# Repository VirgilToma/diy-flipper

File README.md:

# DIY Flipper-style Multitool

A handheld, battery-powered hacking and learning multitool inspired by the Flipper Zero, built around an **ESP32-S3**. It brings together Sub-GHz radio, NFC, 125 kHz RFID, infrared, iButton, a microSD card, an OLED display with a D-pad, Wi-Fi and Bluetooth LE on one 130 x 64 mm board, and it will run its own custom firmware.

*Render generated from the KiCad files. The board has not been built yet.*

> **Note:** This is an independent hobby project. It is **not** affiliated with Flipper Devices and is **not** compatible with the official Flipper Zero firmware.

## Project status

| Part | Status | Details |
|---|---|---|
| Hardware (PCB rev 0.5) | Schematic and 2-layer PCB done, ERC and DRC clean. Not ordered or built yet. | [hardware/](hardware/README.md) |
| Firmware | Not started | [firmware/](firmware/README.md) |
| Enclosure | Not started | [enclosure/](enclosure/README.md) |

## What it does

| Function | Hardware |
|---|---|
| MCU, Wi-Fi, Bluetooth LE, USB | ESP32-S3-WROOM-1-N16R2, native USB-C for flashing, serial console and HID |
| Display and controls | 1.3" 128x64 OLED, D-pad (Up / Down / Left / Right / OK) and Back button |
| Sub-GHz radio | CC1101 module |
| NFC (13.56 MHz) | PN532 module |
| RFID (125 kHz) | Discrete reader front end *(experimental)* |
| Infrared | IR receiver and 940 nm IR LED |
| iButton | 1-Wire contacts |
| Storage | microSD card |
| Feedback | RGB LED, buzzer, vibration motor |
| Expansion | 2x9 GPIO header |
| Power | Li-Po battery with USB-C charging |

The full hardware description (schematic, PCB, parts list, assembly and pin map) is in [hardware/README.md](hardware/README.md).

## Repository structure

```
diy-flipper/
├── hardware/     KiCad project of the main PCB (schematic, PCB, symbol library, 3D model)
├── firmware/     custom ESP32-S3 firmware (not started yet)
├── enclosure/    3D-printable case (not started yet)
└── docs/         schematic PDF, bill of materials and the images used in the READMEs
```

Each folder has its own README:

- **[hardware/](hardware/README.md):** how the board works, the PCB, the parts to buy, assembly notes, the ESP32-S3 pin map and the checklist before ordering.
- **[firmware/](firmware/README.md):** target hardware for the firmware, which peripheral sits on which pin, and how to flash the board.
- **[enclosure/](enclosure/README.md):** board dimensions, parts that stick out of the board and the openings the case needs.
- **[docs/](docs/README.md):** what each document and image is and where it comes from.

## Getting started

- **Just looking:** open the [schematic PDF](docs/schematic.pdf) and the [bill of materials](docs/BOM.csv).
- **Editing the board:** install KiCad 10 or newer and open `hardware/diy_flipper.kicad_pro`. Keep the whole `hardware/` folder together.
- **Building one:** read the [hardware README](hardware/README.md), especially [Bill of materials](hardware/README.md#bill-of-materials), [Assembly notes](hardware/README.md#assembly-notes) and [Before ordering the PCB](hardware/README.md#before-ordering-the-pcb).

## Compared with a real Flipper Zero

- Each CC1101 module covers a single Sub-GHz band.
- PN532 card emulation is limited.
- The 125 kHz RFID front end is experimental and will need bench tuning.
- 5 V on the GPIO header is available only while USB is connected.
- No fuel gauge; the battery level is estimated from its voltage.

## Roadmap

- [x] Schematic
- [x] Component placement and 2-layer PCB routing
- [x] Bill of materials and module pinouts checked against the board
- [x] ERC and DRC in KiCad
- [ ] PCB order
- [ ] First prototype build and bring-up
- [ ] Custom firmware (display UI, input, SD card, IR, NFC, Sub-GHz, RFID, iButton)
- [ ] Enclosure

## Responsible use

This device is meant for learning and for working with your own hardware, cards and remotes. Transmitting on radio frequencies, and reading or copying access cards you do not own, may be restricted or illegal where you live. Check your local regulations and only use it on equipment you are authorized to test.

## License

*To be added* (for example CERN-OHL-S for the hardware and enclosure, and MIT or GPL for the firmware).

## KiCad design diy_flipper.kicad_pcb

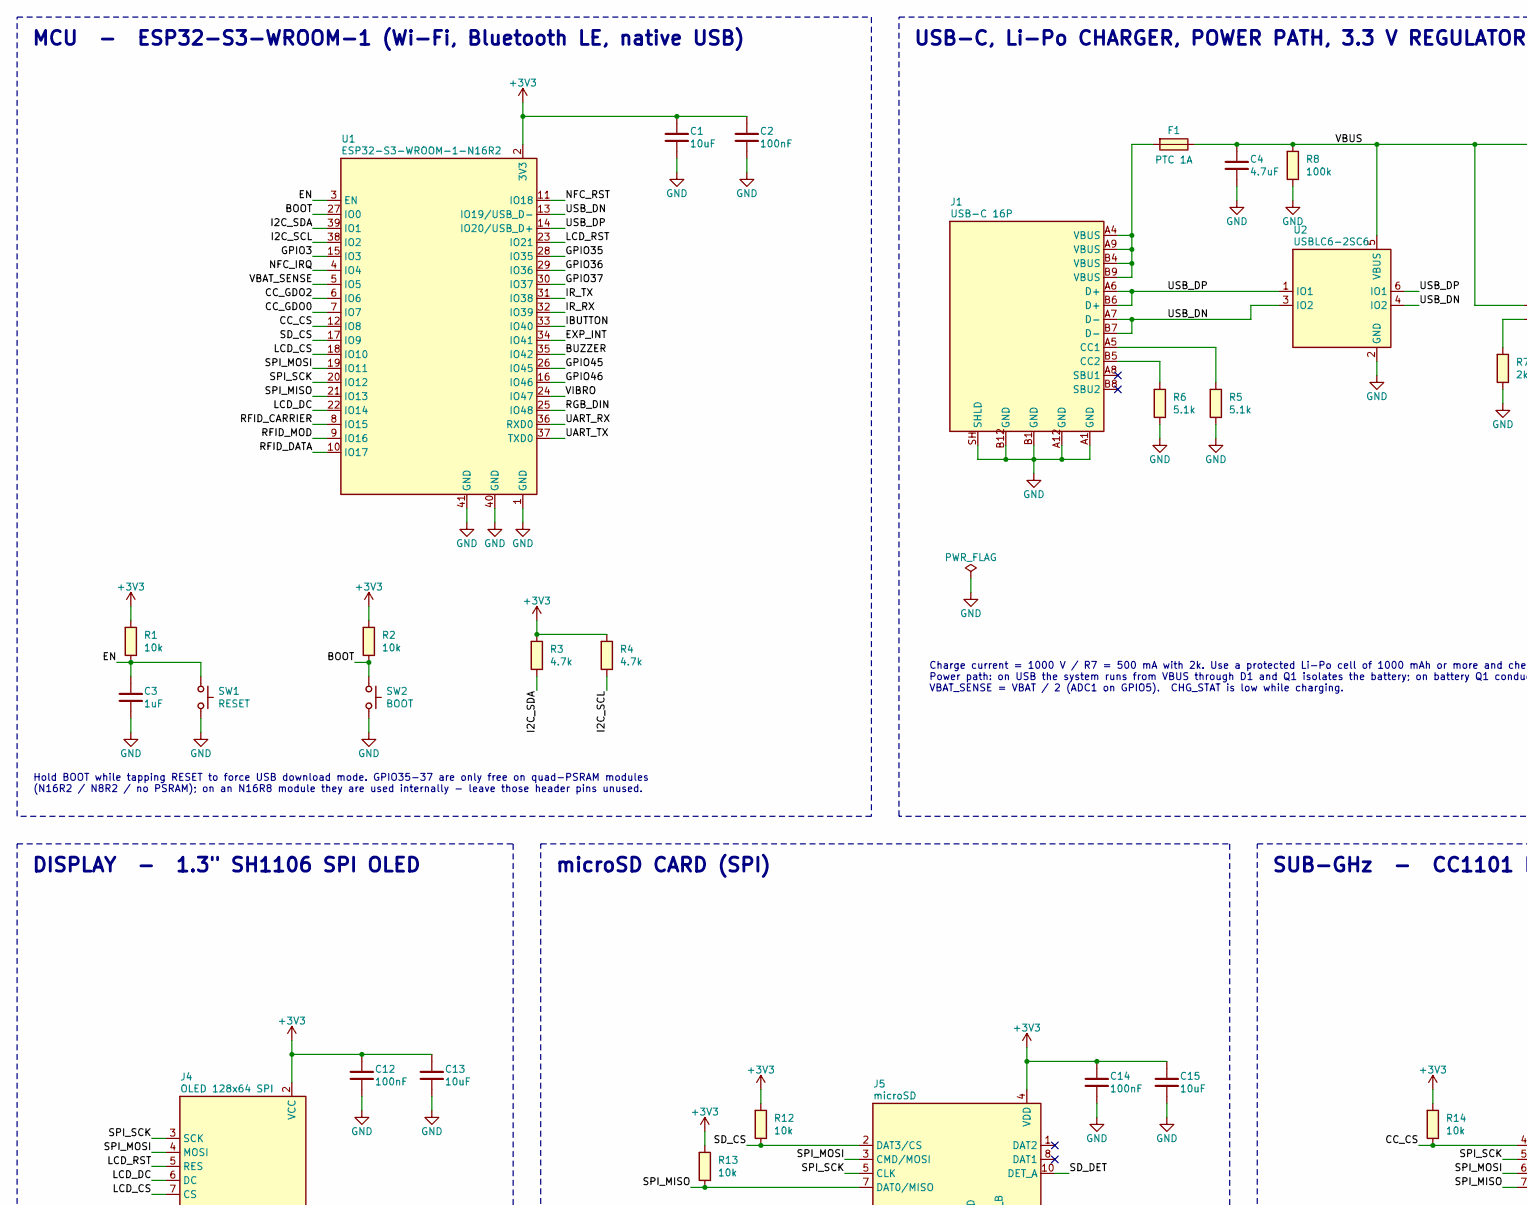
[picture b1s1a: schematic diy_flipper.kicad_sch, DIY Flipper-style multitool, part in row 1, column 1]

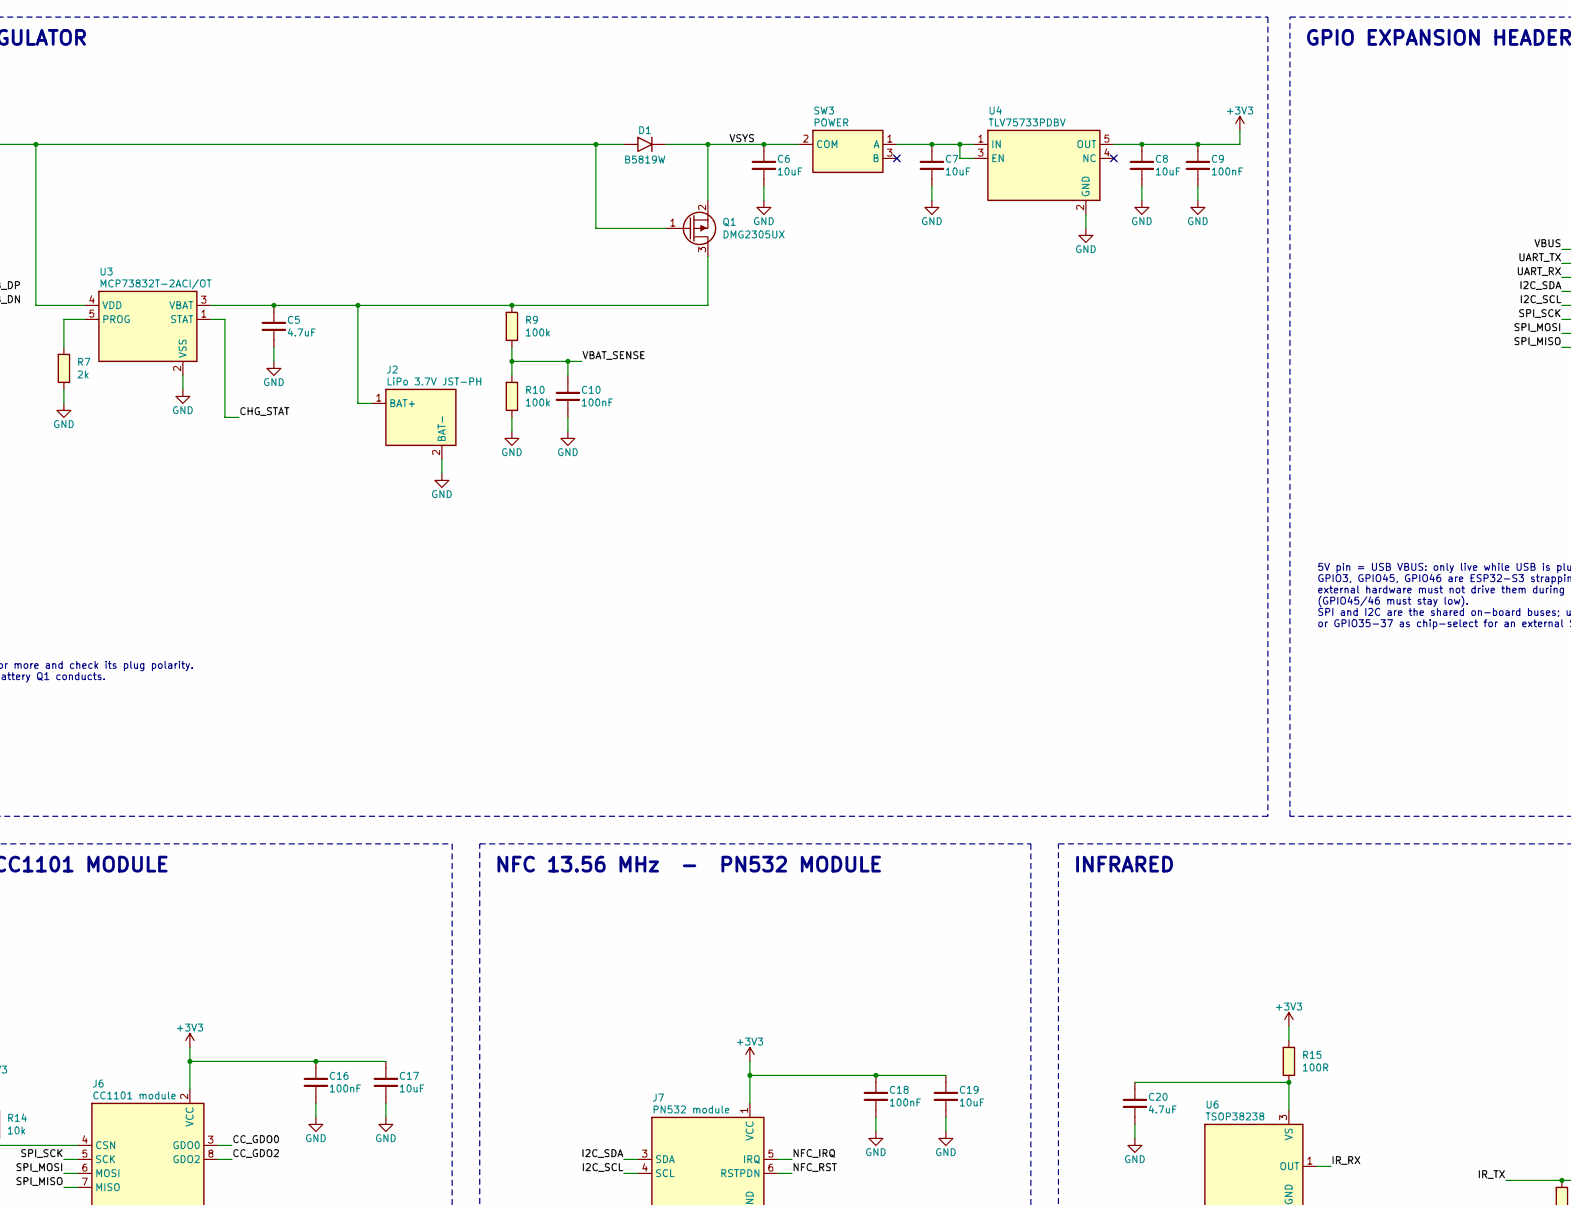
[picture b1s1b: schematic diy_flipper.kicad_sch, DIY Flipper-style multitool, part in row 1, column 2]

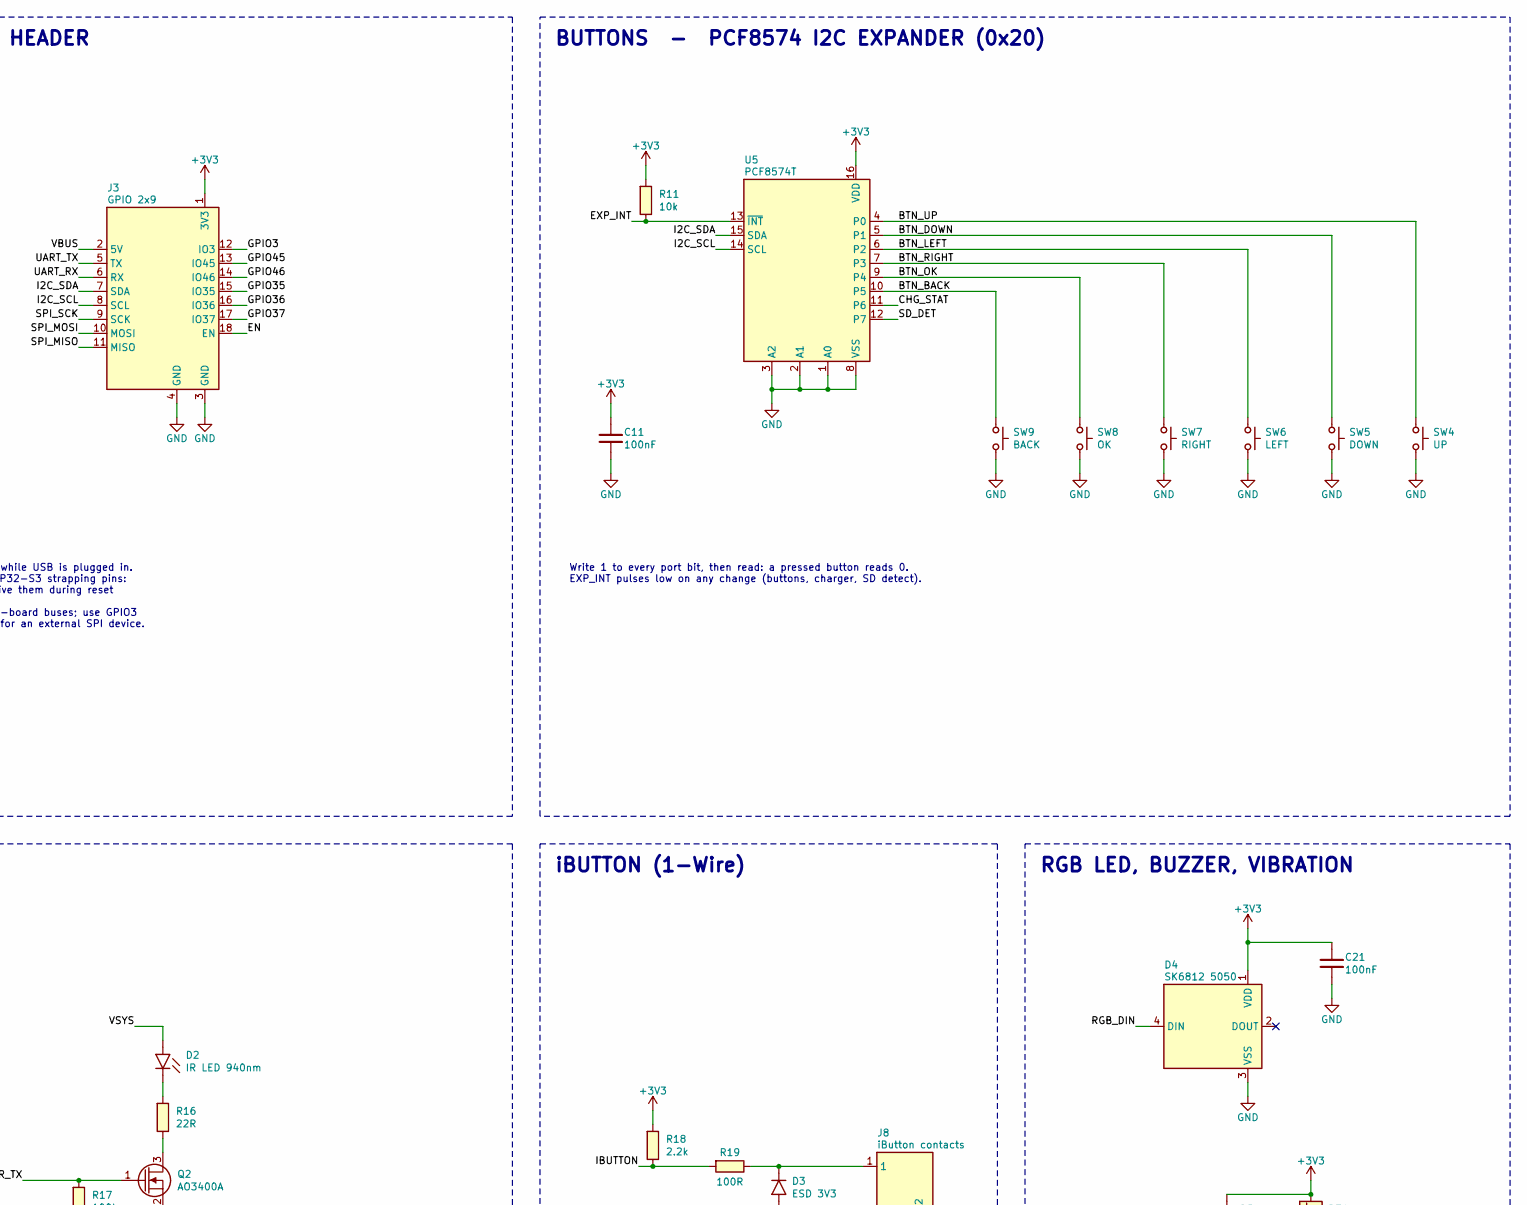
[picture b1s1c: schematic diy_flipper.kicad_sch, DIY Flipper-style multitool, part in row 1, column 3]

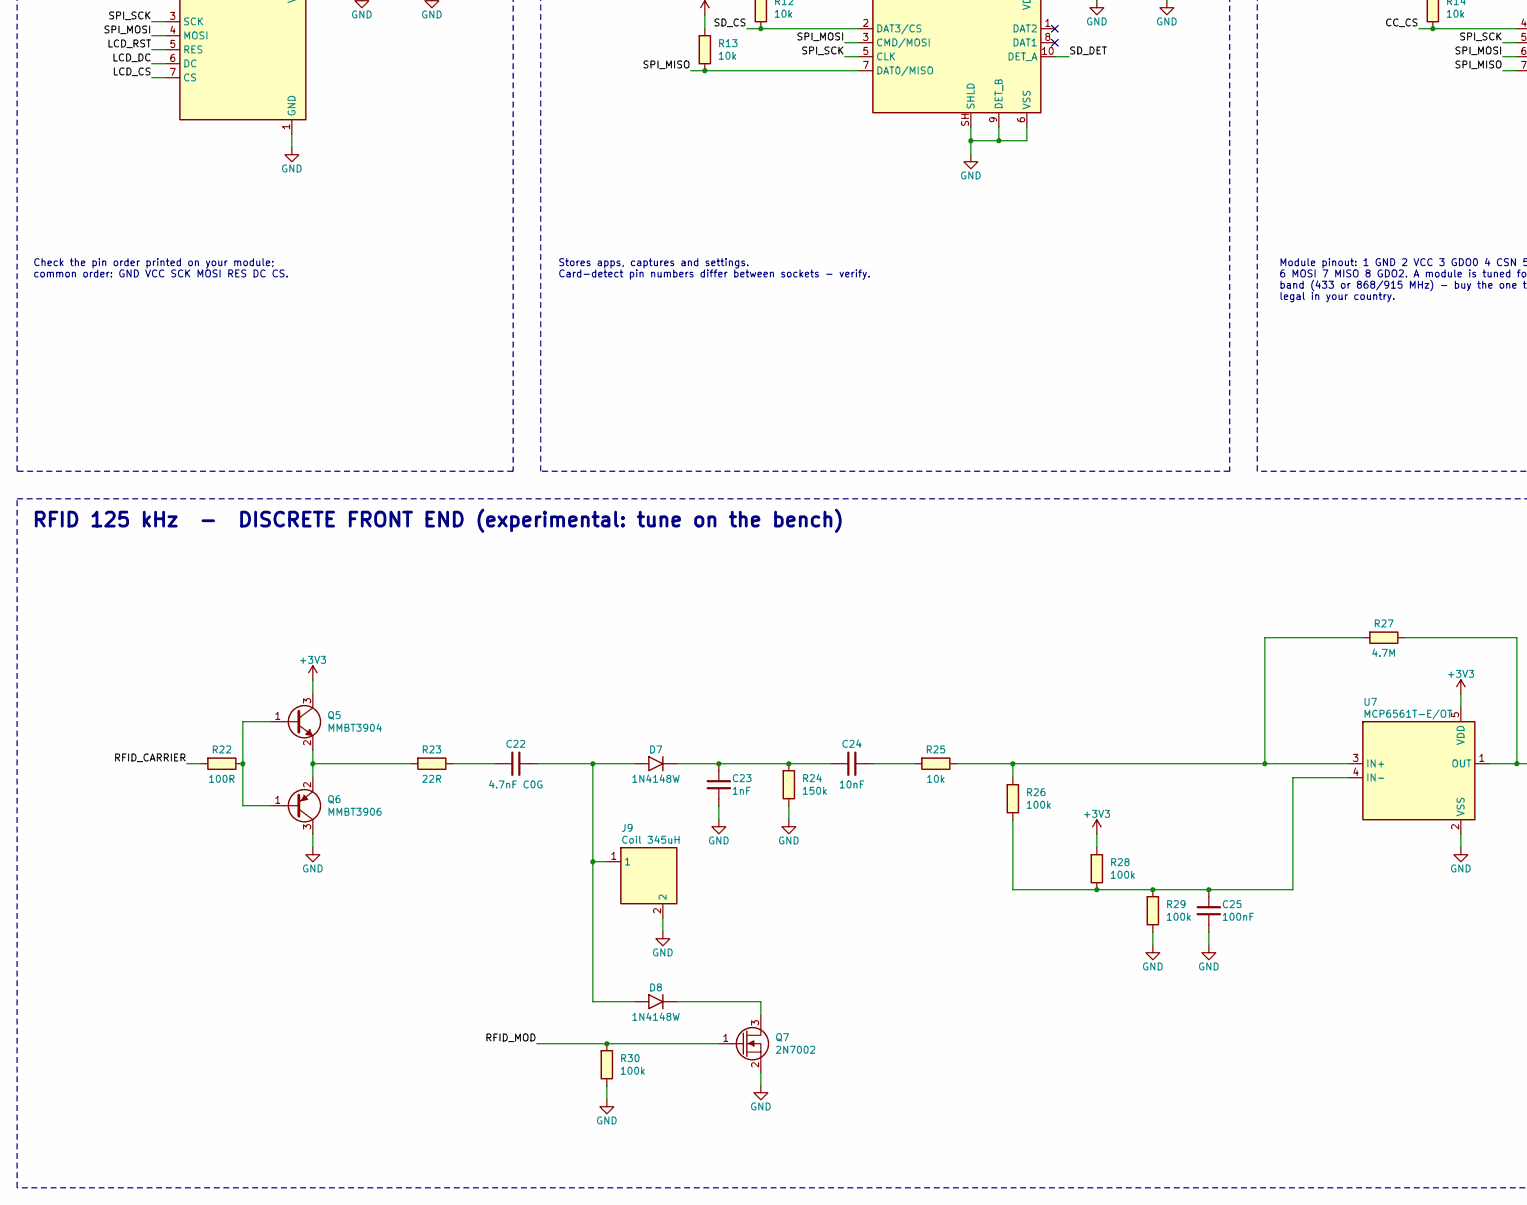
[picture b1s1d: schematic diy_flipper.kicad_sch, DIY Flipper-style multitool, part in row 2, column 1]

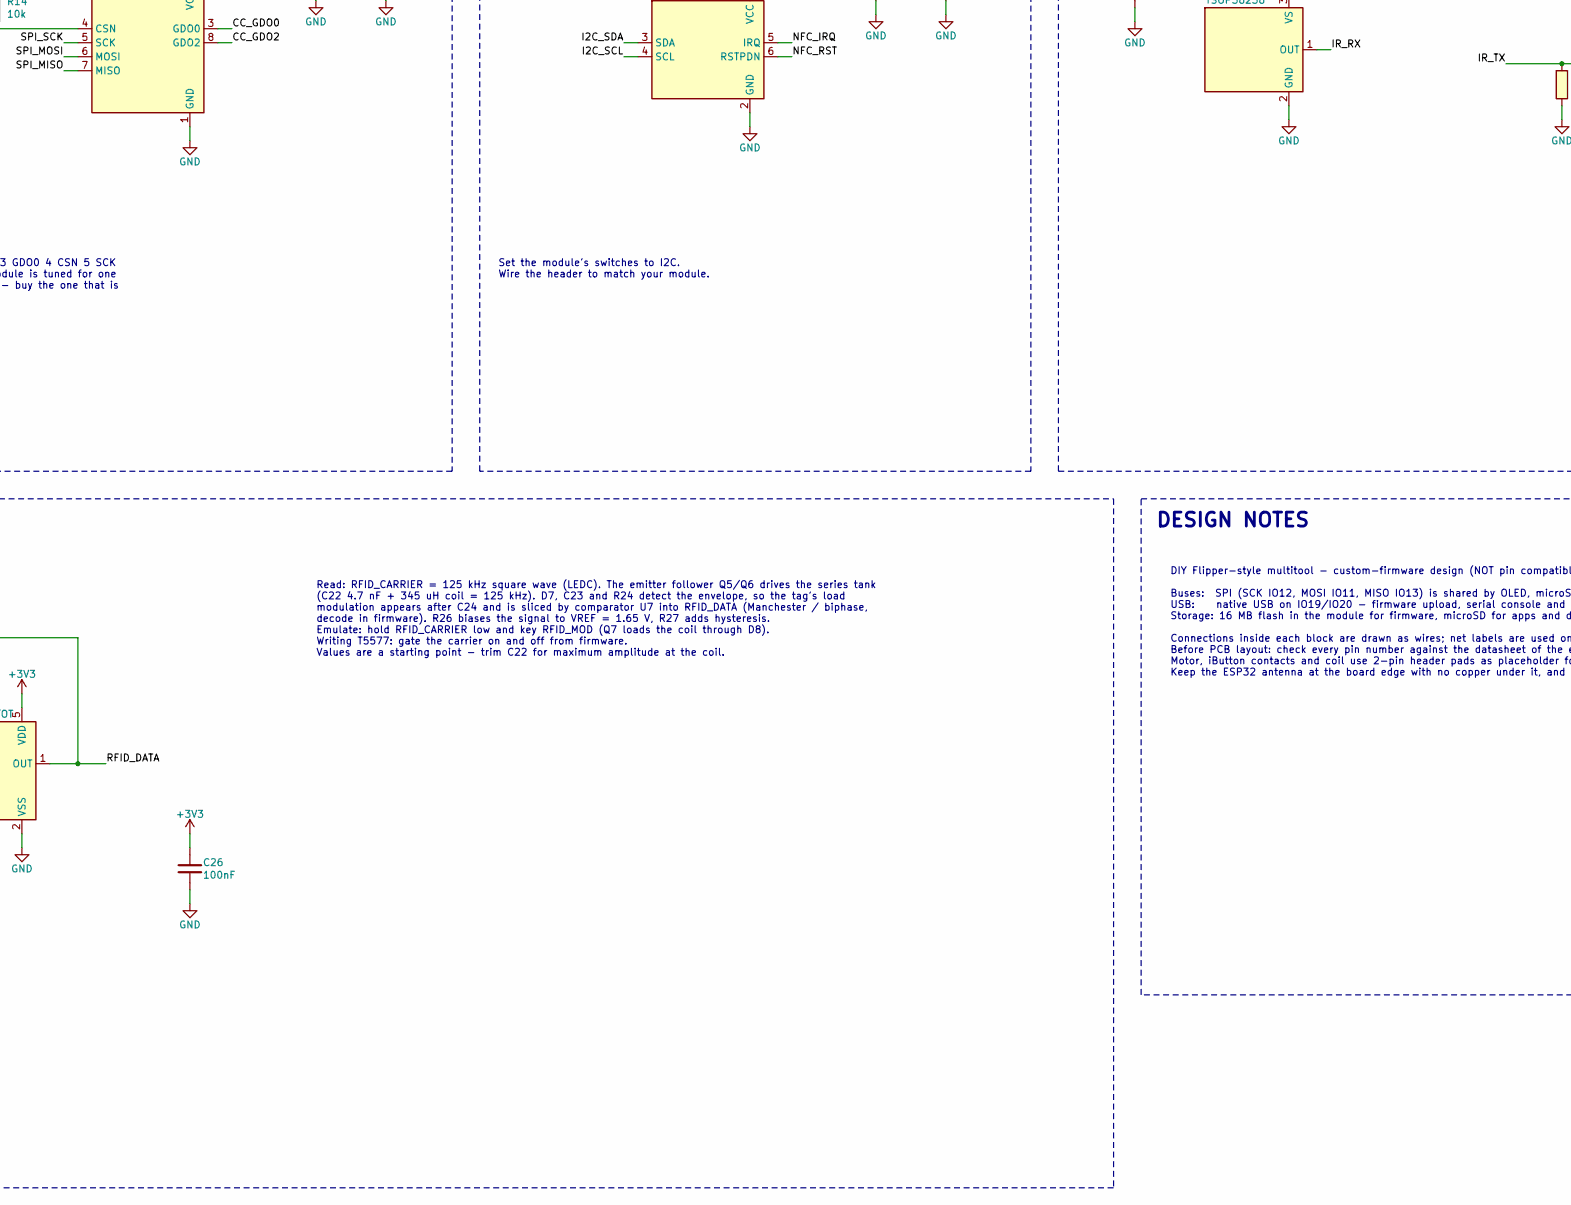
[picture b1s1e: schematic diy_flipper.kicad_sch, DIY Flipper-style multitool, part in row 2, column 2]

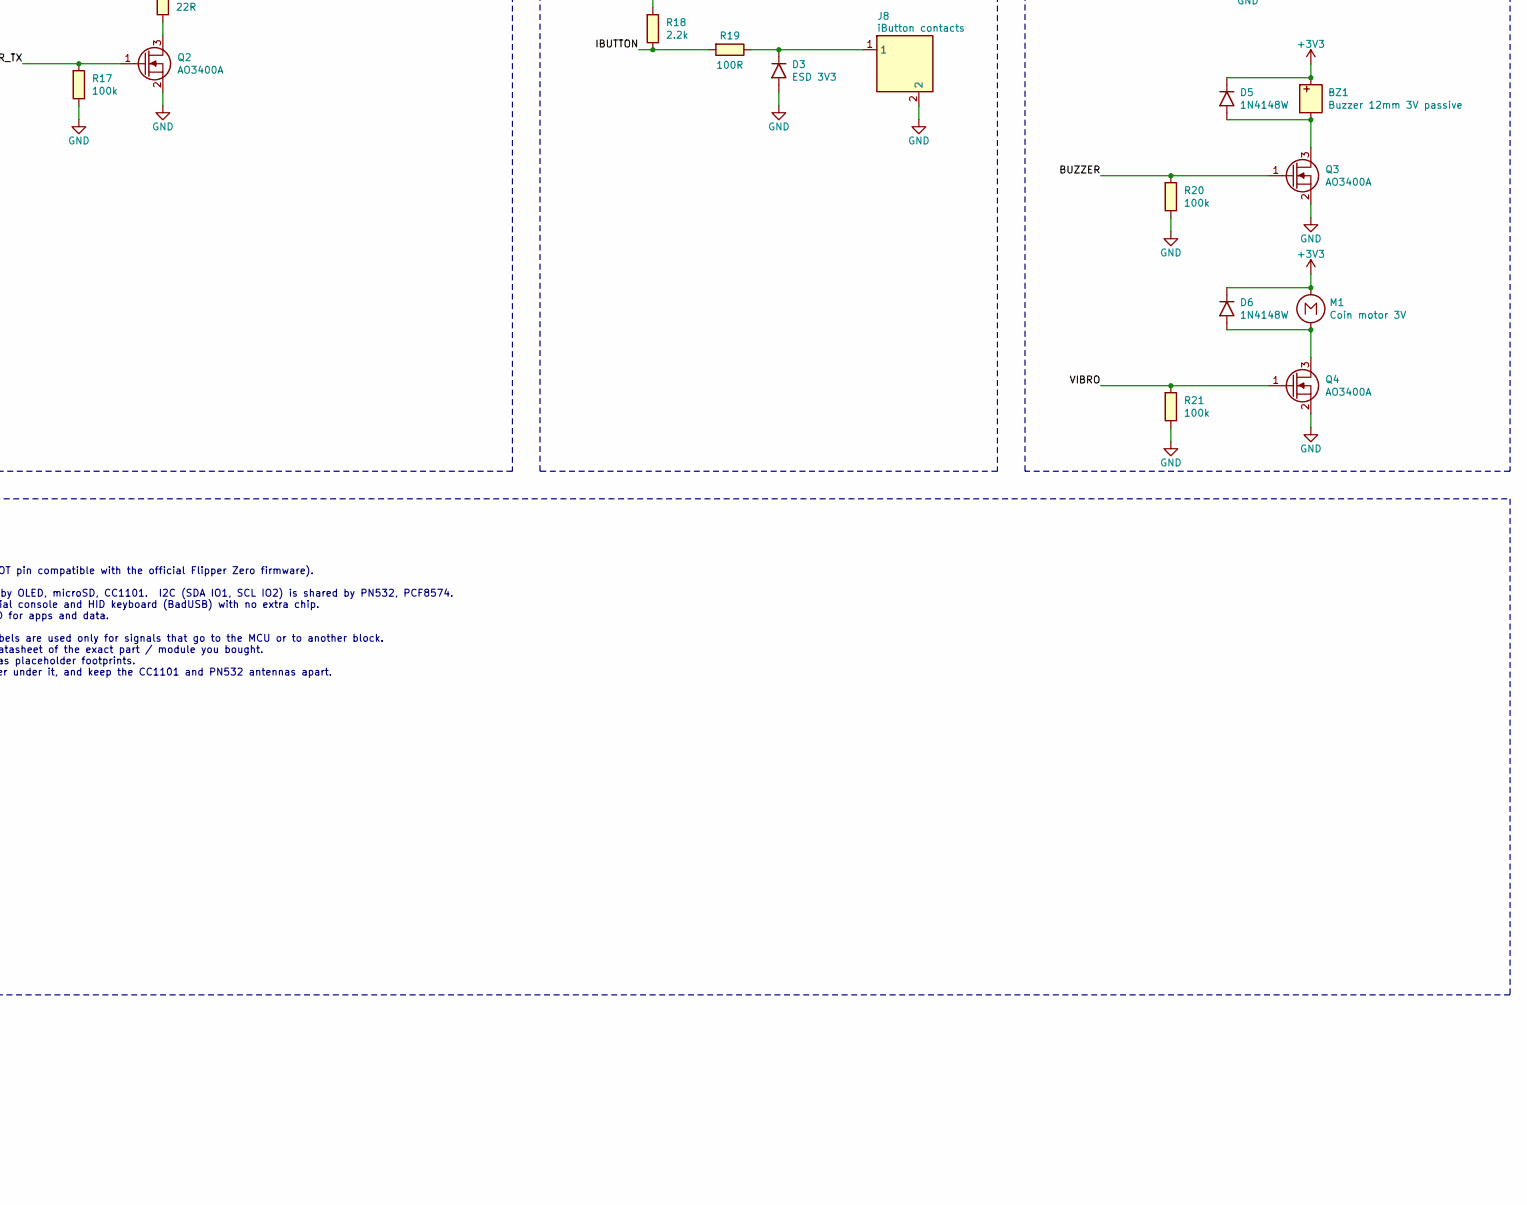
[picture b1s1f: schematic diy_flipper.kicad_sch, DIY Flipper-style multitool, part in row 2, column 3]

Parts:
BZ1: Buzzer 12mm 3V passive; Buzzer_12x9.5RM7.6
C1, C6, C7, C8, C13, C15, C17, C19: 10uF; C_0805_2012Metric
C2, C9, C10, C11, C12, C14, C16, C18, C21, C25, C26: 100nF; C_0603_1608Metric
C3: 1uF; C_0603_1608Metric
C4, C5, C20: 4.7uF; C_0805_2012Metric
C22: 4.7nF C0G; C_0603_1608Metric
C23: 1nF; C_0603_1608Metric
C24: 10nF; C_0603_1608Metric
D1: B5819W; D_SOD-123
D2: IR LED 940nm; LED_D5.0mm
D3: ESD 3V3; D_SOD-323
D4: SK6812 5050; LED_SK6812_PLCC4_5.0x5.0mm_P3.2mm
D5, D6, D7, D8: 1N4148W; D_SOD-123
F1: PTC 1A; Fuse_1206_3216Metric
J1: USB-C 16P; USB_C_Receptacle_HRO_TYPE-C-31-M-12
J2: LiPo 3.7V JST-PH; JST_PH_S2B-PH-K_1x02_P2.00mm_Horizontal
J3: GPIO 2x9; PinHeader_2x09_P2.54mm_Vertical
J4: OLED 128x64 SPI; PinHeader_1x07_P2.54mm_Vertical
J5: microSD; microSD_HC_Hirose_DM3AT-SF-PEJM5
J6: CC1101 module; PinHeader_2x04_P2.54mm_Vertical
J7: PN532 module; PinHeader_1x06_P2.54mm_Vertical
J8: iButton contacts; PinHeader_1x02_P2.54mm_Vertical
J9: Coil 345uH; PinHeader_1x02_P2.54mm_Vertical
M1: Coin motor 3V; PinHeader_1x02_P2.54mm_Vertical
Q1: DMG2305UX; SOT-23
Q2, Q3, Q4: AO3400A; SOT-23
Q5: MMBT3904; SOT-23
Q6: MMBT3906; SOT-23
Q7: 2N7002; SOT-23
R1, R2, R11, R12, R13, R14, R25: 10k; R_0603_1608Metric
R3, R4: 4.7k; R_0603_1608Metric
R5, R6: 5.1k; R_0603_1608Metric
R7: 2k; R_0603_1608Metric
R8, R9, R10, R17, R20, R21, R26, R28, R29, R30: 100k; R_0603_1608Metric
R15, R19, R22: 100R; R_0603_1608Metric
R16: 22R; R_1206_3216Metric
R18: 2.2k; R_0603_1608Metric
R23: 22R; R_0603_1608Metric
R24: 150k; R_0603_1608Metric
R27: 4.7M; R_0603_1608Metric
SW1: RESET; SW_PUSH_6mm
SW2: BOOT; SW_PUSH_6mm
SW3: POWER; SW_SPDT_PCM12
SW4: UP; SW_PUSH_6mm
SW5: DOWN; SW_PUSH_6mm
SW6: LEFT; SW_PUSH_6mm
SW7: RIGHT; SW_PUSH_6mm
SW8: OK; SW_PUSH_6mm
SW9: BACK; SW_PUSH_6mm
U1: ESP32-S3-WROOM-1-N16R2; ESP32-S3-WROOM-1
U2: USBLC6-2SC6; SOT-23-6
U3: MCP73832T-2ACI/OT; SOT-23-5
U4: TLV75733PDBV; SOT-23-5
U5: PCF8574T; SOIC-16W_7.5x10.3mm_P1.27mm
U6: TSOP38238; Vishay_MINICAST-3Pin
U7: MCP6561T-E/OT; SOT-23-5

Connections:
+3V3: BZ1.1, C1.1, C2.1, C8.1, C9.1, C11.1, C12.1, C13.1, C14.1, C15.1, C16.1, C17.1, C18.1, C19.1, C21.1, C26.1, D4.1 (VDD), D5.1, D6.1, J3.1 (3V3), J4.2 (VCC), J5.4 (VDD), J6.2 (VCC), J7.1 (VCC), M1.1, Q5.3, R1.1, R2.1, R3.1, R4.1, R11.1, R12.1, R13.1, R14.1, R15.1, R18.1, R28.1, U1.2 (3V3), U4.5 (OUT), U5.16 (VDD), U7.5 (VDD)
/BOOT: R2.2, SW2.1, U1.27 (IO0)
/BTN_BACK: SW9.1, U5.10 (P5)
/BTN_DOWN: SW5.1, U5.5 (P1)
/BTN_LEFT: SW6.1, U5.6 (P2)
/BTN_OK: SW8.1, U5.9 (P4)
/BTN_RIGHT: SW7.1, U5.7 (P3)
/BTN_UP: SW4.1, U5.4 (P0)
/BUZZER: Q3.1, R20.1, U1.35 (IO42)
/BUZ_D: BZ1.2, D5.2, Q3.3
/CC_CS: J6.4 (CSN), R14.2, U1.12 (IO8)
/CC_GDO0: J6.3 (GDO0), U1.7 (IO7)
/CC_GDO2: J6.8 (GDO2), U1.6 (IO6)
/CHG_PROG: R7.1, U3.5 (PROG)
/CHG_STAT: U3.1 (STAT), U5.11 (P6)
/EN: C3.1, J3.18 (EN), R1.2, SW1.1, U1.3 (EN)
/EXP_INT: R11.2, U1.34 (IO41), U5.13 (~INT)
/GPIO3: J3.12 (IO3), U1.15 (IO3)
/GPIO35: J3.15 (IO35), U1.28 (IO35)
/GPIO36: J3.16 (IO36), U1.29 (IO36)
/GPIO37: J3.17 (IO37), U1.30 (IO37)
/GPIO45: J3.13 (IO45), U1.26 (IO45)
/GPIO46: J3.14 (IO46), U1.16 (IO46)
/I2C_SCL: J3.8 (SCL), J7.4 (SCL), R4.2, U1.38 (IO2), U5.14 (SCL)
/I2C_SDA: J3.7 (SDA), J7.3 (SDA), R3.2, U1.39 (IO1), U5.15 (SDA)
/IBTN_PAD: D3.1, J8.1, R19.2
/IBUTTON: R18.2, R19.1, U1.33 (IO40)
/IR_DRAIN: Q2.3, R16.2
/IR_LED_K: D2.1, R16.1
/IR_RX: U1.32 (IO39), U6.1 (OUT)
/IR_TX: Q2.1, R17.1, U1.31 (IO38)
/IR_VS: C20.1, R15.2, U6.3 (VS)
/LCD_CS: J4.7 (CS), U1.18 (IO10)
/LCD_DC: J4.6 (DC), U1.22 (IO14)
/LCD_RST: J4.5 (RES), U1.23 (IO21)
/NFC_IRQ: J7.5 (IRQ), U1.4 (IO4)
/NFC_RST: J7.6 (RSTPDN), U1.11 (IO18)
/RFID_AC: C24.2, R25.1
/RFID_ANT: C22.2, D7.2, D8.2, J9.1
/RFID_BASE: Q5.1, Q6.1, R22.2
/RFID_CARRIER: R22.1, U1.8 (IO15)
/RFID_DRV: Q5.2, Q6.2, R23.1
/RFID_EMU_D: D8.1, Q7.3
/RFID_ENV: C23.1, C24.1, D7.1, R24.1
/RFID_MOD: Q7.1, R30.1, U1.9 (IO16)
/RFID_TANK: C22.1, R23.2
/RFID_VREF: C25.1, R26.2, R28.2, R29.1, U7.4 (IN-)
/RGB_DIN: D4.4 (DIN), U1.25 (IO48)
/SD_CS: J5.2 (DAT3/CS), R12.2, U1.17 (IO9)
/SD_DET: J5.10 (DET_A), U5.12 (P7)
/SPI_MISO: J3.11 (MISO), J5.7 (DAT0/MISO), J6.7 (MISO), R13.2, U1.21 (IO13)
/SPI_MOSI: J3.10 (MOSI), J4.4 (MOSI), J5.3 (CMD/MOSI), J6.6 (MOSI), U1.19 (IO11)
/SPI_SCK: J3.9 (SCK), J4.3 (SCK), J5.5 (CLK), J6.5 (SCK), U1.20 (IO12)
/UART_RX: J3.6 (RX), U1.36 (RXD0)
/UART_TX: J3.5 (TX), U1.37 (TXD0)
/USB_CC1: J1.A5 (CC1), R5.1
/USB_CC2: J1.B5 (CC2), R6.1
/USB_DN: J1.A7 (D-), J1.B7 (D-), U1.13 (IO19/USB_D-), U2.3 (IO2), U2.4 (IO2)
/USB_DP: J1.A6 (D+), J1.B6 (D+), U1.14 (IO20/USB_D+), U2.1 (IO1), U2.6 (IO1)
/USB_VBUS: F1.1, J1.A4 (VBUS), J1.A9 (VBUS), J1.B4 (VBUS), J1.B9 (VBUS)
/VBAT: C5.1, J2.1 (BAT+), Q1.3, R9.1, U3.3 (VBAT)
/VBAT_SENSE: C10.1, R9.2, R10.1, U1.5 (IO5)
/VBUS: C4.1, D1.2, F1.2, J3.2 (5V), Q1.1, R8.1, U2.5 (VBUS), U3.4 (VDD)
/VIBRO: Q4.1, R21.1, U1.24 (IO47)
/VIB_D: D6.2, M1.2, Q4.3
/VSW: C7.1, SW3.1 (A), U4.1 (IN), U4.3 (EN)
/VSYS: C6.1, D1.1, D2.2, Q1.2, SW3.2 (COM)
GND: C1.2, C2.2, C3.2, C4.2, C5.2, C6.2, C7.2, C8.2, C9.2, C10.2, C11.2, C12.2, C13.2, C14.2, C15.2, C16.2, C17.2, C18.2, C19.2, C20.2, C21.2, C23.2, C25.2, C26.2, D3.2, D4.3 (VSS), J1.A1 (GND), J1.A12 (GND), J1.B1 (GND), J1.B12 (GND), J1.SH (SHLD), J2.2 (BAT-), J3.3 (GND), J3.4 (GND), J4.1 (GND), J5.6 (VSS), J5.9 (DET_B), J5.SH (SHLD), J6.1 (GND), J7.2 (GND), J8.2, J9.2, Q2.2, Q3.2, Q4.2, Q6.3, Q7.2, R5.2, R6.2, R7.2, R8.2, R10.2, R17.2, R20.2, R21.2, R24.2, R29.2, R30.2, SW1.2, SW2.2, SW4.2, SW5.2, SW6.2, SW7.2, SW8.2, SW9.2, U1.1 (GND), U1.40 (GND), U1.41 (GND), U2.2 (GND), U3.2 (VSS), U4.2 (GND), U5.1 (A0), U5.2 (A1), U5.3 (A2), U5.8 (VSS), U6.2 (GND), U7.2 (VSS)

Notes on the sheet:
Set the module's switches to I2C. Wire the header to match your module.
Stores apps, captures and settings. Card-detect pin numbers differ between sockets - verify.
SUB-GHz - CC1101 MODULE
DIY Flipper-style multitool - custom-firmware design (NOT pin compatible with the official Flipper Zero firmware). Buses: SPI (SCK IO12, MOSI IO11, MISO IO13) is shared by OLED, microSD, CC1101. I2C (SDA IO1, SCL IO2) is shared by PN532, PCF8574. USB: native USB on IO19/IO20 - firmware upload, seri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
GPIO EXPANSION HEADER
Write 1 to every port bit, then read: a pressed button reads 0. EXP_INT pulses low on any change (buttons, charger, SD detect).
DESIGN NOTES
Check the pin order printed on your module; common order: GND VCC SCK MOSI RES DC CS.
microSD CARD (SPI)
RFID 125 kHz - DISCRETE FRONT END (experimental: tune on the bench)
DISPLAY - 1.3" SH1106 SPI OLED
Hold BOOT while tapping RESET to force USB download mode. GPIO35-37 are only free on quad-PSRAM modules (N16R2 / N8R2 / no PSRAM); on an N16R8 module they are used internally - leave those header pins unused.
Read: RFID_CARRIER = 125 kHz square wave (LEDC). The emitter follower Q5/Q6 drives the series tank (C22 4.7 nF + 345 uH coil = 125 kHz). D7, C23 and R24 detect the envelope, so the tag's load modulation appears after C24 and is sliced by comparator U7 into RFID_DATA (Manchester / biphase, decode in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
NFC 13.56 MHz - PN532 MODULE
iBUTTON (1-Wire)
Charge current = 1000 V / R7 = 500 mA with 2k. Use a protected Li-Po cell of 1000 mAh or more and check its plug polarity. Power path: on USB the system runs from VBUS through D1 and Q1 isolates the battery; on battery Q1 conducts. VBAT_SENSE = VBAT / 2 (ADC1 on GPIO5). CHG_STAT is low while chargi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
MCU - ESP32-S3-WROOM-1 (Wi-Fi, Bluetooth LE, native USB)
INFRARED
USB-C, Li-Po CHARGER, POWER PATH, 3.3 V REGULATOR
BUTTONS - PCF8574 I2C EXPANDER (0x20)
5V pin = USB VBUS: only live while USB is plugged in. GPIO3, GPIO45, GPIO46 are ESP32-S3 strapping pins: external hardware must not drive them during reset (GPIO45/46 must stay low). SPI and I2C are the shared on-board buses; use GPIO3 or GPIO35-37 as chip-select for an external SPI device.
Module pinout: 1 GND 2 VCC 3 GDO0 4 CSN 5 SCK 6 MOSI 7 MISO 8 GDO2. A module is tuned for one band (433 or 868/915 MHz) - buy the one that is legal in your country.
RGB LED, BUZZER, VIBRATION

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
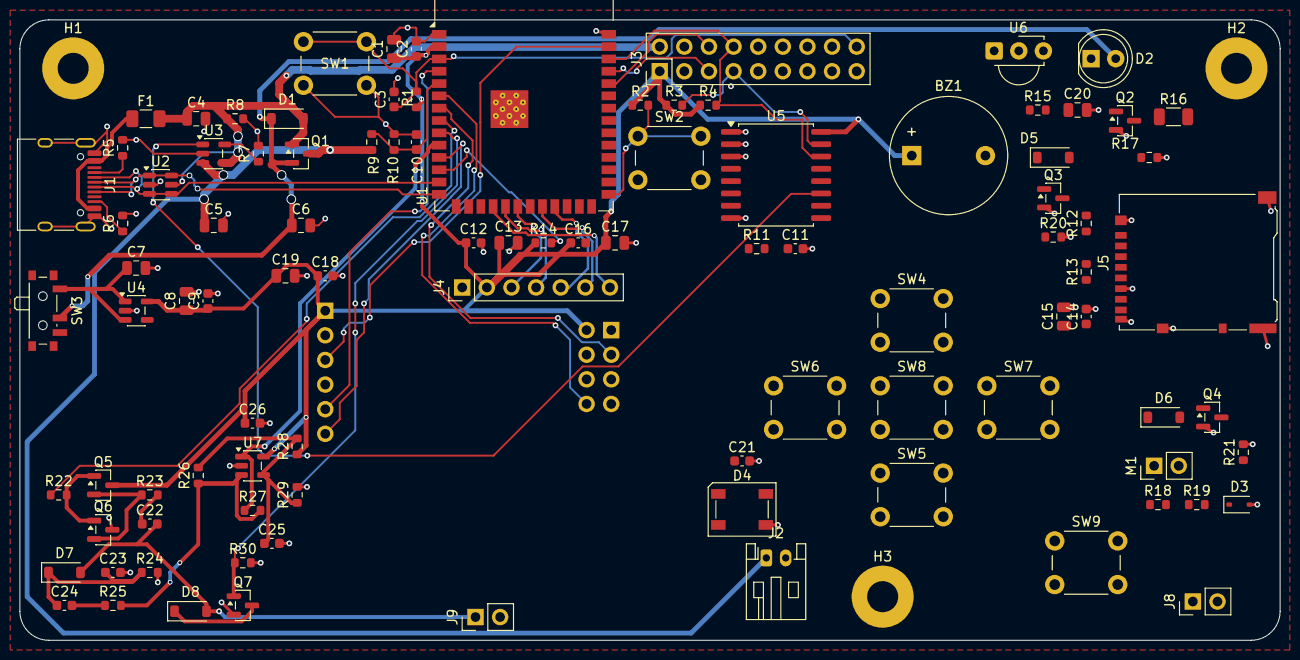
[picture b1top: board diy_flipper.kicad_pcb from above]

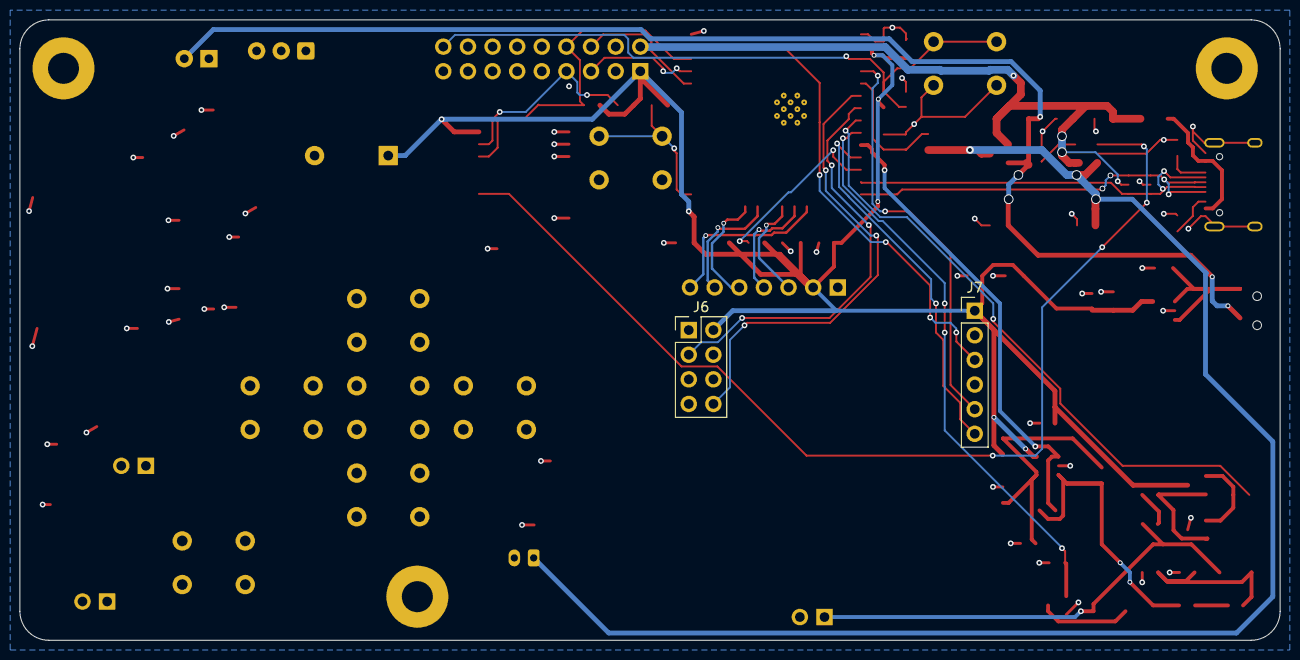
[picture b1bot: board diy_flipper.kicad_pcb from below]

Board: 2 copper layers, 130.0 x 64.0 mm, 102 parts (2 on the bottom side), 70 nets.

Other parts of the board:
H1, H2, H3: MountingHole_3.2mm_M3_Pad

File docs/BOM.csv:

Reference,Qty,Part,Package,Suggested part number,Function,Notes
U1,1,ESP32-S3-WROOM-1-N16R2,SMD module 18 x 25.5 mm,Espressif ESP32-S3-WROOM-1-N16R2,"MCU, Wi-Fi, BLE, USB","Exactly N16R2 (16 MB flash, 2 MB quad PSRAM). Not N16R8 / N8R8: on those GPIO35-37 are used by the octal PSRAM."
J4 (module),1,"1.3"" OLED 128x64, SH1106, SPI, 7 pins",module 35.4 x 33.5 mm,"Pololu 3761 or equivalent ""1.3 inch OLED SPI 7 pin SH1106""",Display,"Pin order must be GND, VCC, CLK, MOSI, RES, DC, CS. Not the 4-pin I2C version. Soldered straight into J4 (no socket)."
J6 (module),1,"CC1101 433 MHz module, 2x4 header",module 15 x 30 mm (+ SMA),EBYTE E07-M1101D-SMA (or E07-M1101D-TH with spring antenna),Sub-GHz radio,"3.6 V max. Generic CC1101 boards use other pin orders: buy the E07. Mounted on the back, see the assembly notes."
J7 (module),1,PN532 NFC module V3 (or V4),module 42.7 x 40.4 mm,Elechouse PN532 NFC Module V3/V4 or the red V3 clone,NFC 13.56 MHz,"I2C mode: S1 = ON, S2 = OFF. Wired to J7 (1x5: GND, VCC, SDA, SCL, IRQ); pins 1-4 follow the module I2C header, IRQ comes from the module top header."
J7 (board),1,"Pin header 1x5, 2.54 mm",THT,-,PN532 connection,Optional: the wires can also be soldered straight into the holes.
BT1 (off board),1,Li-Po 3.7 V 503450 (~1000 mAh) with protection,"50 x 34 x 5 mm, JST-PH 2.0 plug",any 503450 with PCM and JST-PH plug,Power,"Polarity: pin 1 = + (red wire), as on SparkFun/Adafruit. Many RC batteries are reversed: check with a multimeter first."
U2,1,USBLC6-2SC6,SOT-23-6,STMicroelectronics USBLC6-2SC6,USB ESD protection,
U3,1,MCP73832T-2ACI/OT,SOT-23-5,Microchip MCP73832T-2ACI/OT,"Li-Po charger, ~500 mA (R7 = 2 kOhm)",-2A variant = 4.20 V. STAT output is open-drain.
U4,1,TLV75733PDBVR,SOT-23-5 (DBV),Texas Instruments TLV75733PDBVR,"3.3 V LDO, 1 A",DBV package (not DYD/DRV).
U5,1,PCF8574T,SO-16 wide (7.5 mm),NXP PCF8574T/3 or TI PCF8574DWR,"Button expander, I2C 0x20",Not PCF8574A: its address is 0x38.
U6,1,TSOP38238,"Minicast, THT",Vishay TSOP38238,38 kHz IR receiver,TSOP382xx / 384xx family only: other TSOP families swap VS and GND.
U7,1,MCP6561T-E/OT,SOT-23-5,Microchip MCP6561T-E/OT,125 kHz RFID comparator,Not MCP6561R or MCP6561U: different pinout.
Q1,1,DMG2305UX,SOT-23,Diodes Inc. DMG2305UX-7,"P-MOSFET, USB / battery switch-over",
"Q2, Q3, Q4",3,AO3400A,SOT-23,Alpha & Omega AO3400A,"N-MOSFET: IR LED, buzzer, motor",
Q5,1,MMBT3904,SOT-23,onsemi / Nexperia MMBT3904,"NPN, RFID coil driver",
Q6,1,MMBT3906,SOT-23,onsemi / Nexperia MMBT3906,"PNP, RFID coil driver",
Q7,1,2N7002,SOT-23,onsemi / Nexperia 2N7002,"N-MOSFET, RFID emulation",
D1,1,B5819W,SOD-123,"B5819W (Schottky 1 A, 40 V)",VBUS to VSYS diode,
D2,1,"IR LED 940 nm, 5 mm",THT 5 mm,Vishay TSAL6200,IR emitter,"Cathode (short leg, flat side) in the square pad."
D3,1,ESD diode 3.3 V,SOD-323,Nexperia PESD3V3L1BA,iButton contact protection,Bidirectional: orientation does not matter.
D4,1,"SK6812 5050, 4 pins",PLCC4 5 x 5 mm,"OPSCO SK6812 (5050, 4 pins)",Addressable RGB LED,"Pin order 1 VDD, 2 DOUT, 3 VSS, 4 DIN (other variants exist). Rated from 3.5 V, runs at 3.3 V here."
"D5, D6, D7, D8",4,1N4148W,SOD-123,1N4148W,"Buzzer/motor flyback, RFID detector and emulation",
F1,1,Resettable PTC fuse ~1 A,1206,"Bourns MF-NSMF110-2 or equivalent 1206, Ihold ~1.1 A, >= 6 V",VBUS protection,
J1,1,"USB-C receptacle, 16 pins",SMD + THT,HRO TYPE-C-31-M-12,USB 2.0 + power,
J2,1,"JST-PH 2-pin, side entry","THT, 2.0 mm pitch",JST S2B-PH-K-S,Battery,
J3,1,"Pin header 2x9, 2.54 mm",THT,-,GPIO header,
J5,1,microSD push-push socket with card detect,SMD,Hirose DM3AT-SF-PEJM5,microSD card (SPI),
J8,1,iButton contacts,"2 pins, 2.54 mm",iButton probe (e.g. DS9092 style) or own contacts,iButton reader (1-Wire),Placeholder pads: adapt to the contacts you use.
J9,1,"125 kHz antenna coil, ~345 uH",2 wires to 2.54 mm pins,hand-wound or ready-made 125 kHz RFID coil,125 kHz RFID antenna,With C22 = 4.7 nF it resonates at ~125 kHz.
M1,1,"Coin vibration motor, 3 V","10 mm, with wires",e.g. 1027 (10 x 2.7 mm),Vibration,
BZ1,1,"Passive buzzer 12 mm, 3 V","THT, 7.6 mm pitch",passive magnetic buzzer 12 x 9.5 mm,Sound,Passive (no internal oscillator): the firmware drives the tone.
"SW1, SW2, SW4-SW9",8,Tactile switch 6 x 6 mm,THT 6 x 6,Omron B3F-1000 or equivalent,"RESET, BOOT, D-pad, BACK",
SW3,1,Slide switch SPDT,SMD,C&K PCM12SMTR,Power on / off,
"H1, H2, H3",3,M3 screw + standoff,-,-,Enclosure mounting,
"R5, R6",2,5.1 kOhm 1 %,0603,-,USB-C CC1/CC2 (sink),
R7,1,2 kOhm 1 %,0603,-,Charger PROG (~500 mA),
"R1, R2, R11, R12, R13, R14, R25",7,10 kOhm 1 %,0603,-,"Pull-ups: EN, BOOT, INT, chip selects, MISO; RFID",
"R3, R4",2,4.7 kOhm 1 %,0603,-,I2C pull-ups,
"R8, R9, R10, R17, R20, R21, R26, R28, R29, R30",10,100 kOhm 1 %,0603,-,"Gate pull-downs, VBAT divider, RFID",
"R15, R19, R22",3,100 Ohm 1 %,0603,-,"TSOP filter, iButton series, RFID base",
R16,1,22 Ohm 1 %,1206,-,IR LED current limit (~120 mA pulsed),1206 for power.
R23,1,22 Ohm 1 %,0603,-,RFID driver series,
R18,1,2.2 kOhm 1 %,0603,-,1-Wire pull-up,
R24,1,150 kOhm 1 %,0603,-,RFID detector load,
R27,1,4.7 MOhm 1 %,0603,-,Comparator hysteresis,
"C2, C9, C10, C11, C12, C14, C16, C18, C21, C25, C26",11,"100 nF X7R, 16 V",0603,-,Decoupling,
"C1, C6, C7, C8, C13, C15, C17, C19",8,"10 uF X5R, 16 V",0805,-,Supply decoupling,16 V so it keeps enough capacitance at 5 V.
"C4, C5, C20",3,"4.7 uF X5R, 16 V",0805,-,"Charger input/output, TSOP filter",
C3,1,1 uF X7R,0603,-,EN power-on delay,
C22,1,"4.7 nF C0G / NP0, 50 V",0603,-,RFID resonance capacitor,Must be C0G/NP0 (stable).
C23,1,1 nF X7R,0603,-,RFID detector filter,
C24,1,10 nF X7R,0603,-,RFID signal coupling,
